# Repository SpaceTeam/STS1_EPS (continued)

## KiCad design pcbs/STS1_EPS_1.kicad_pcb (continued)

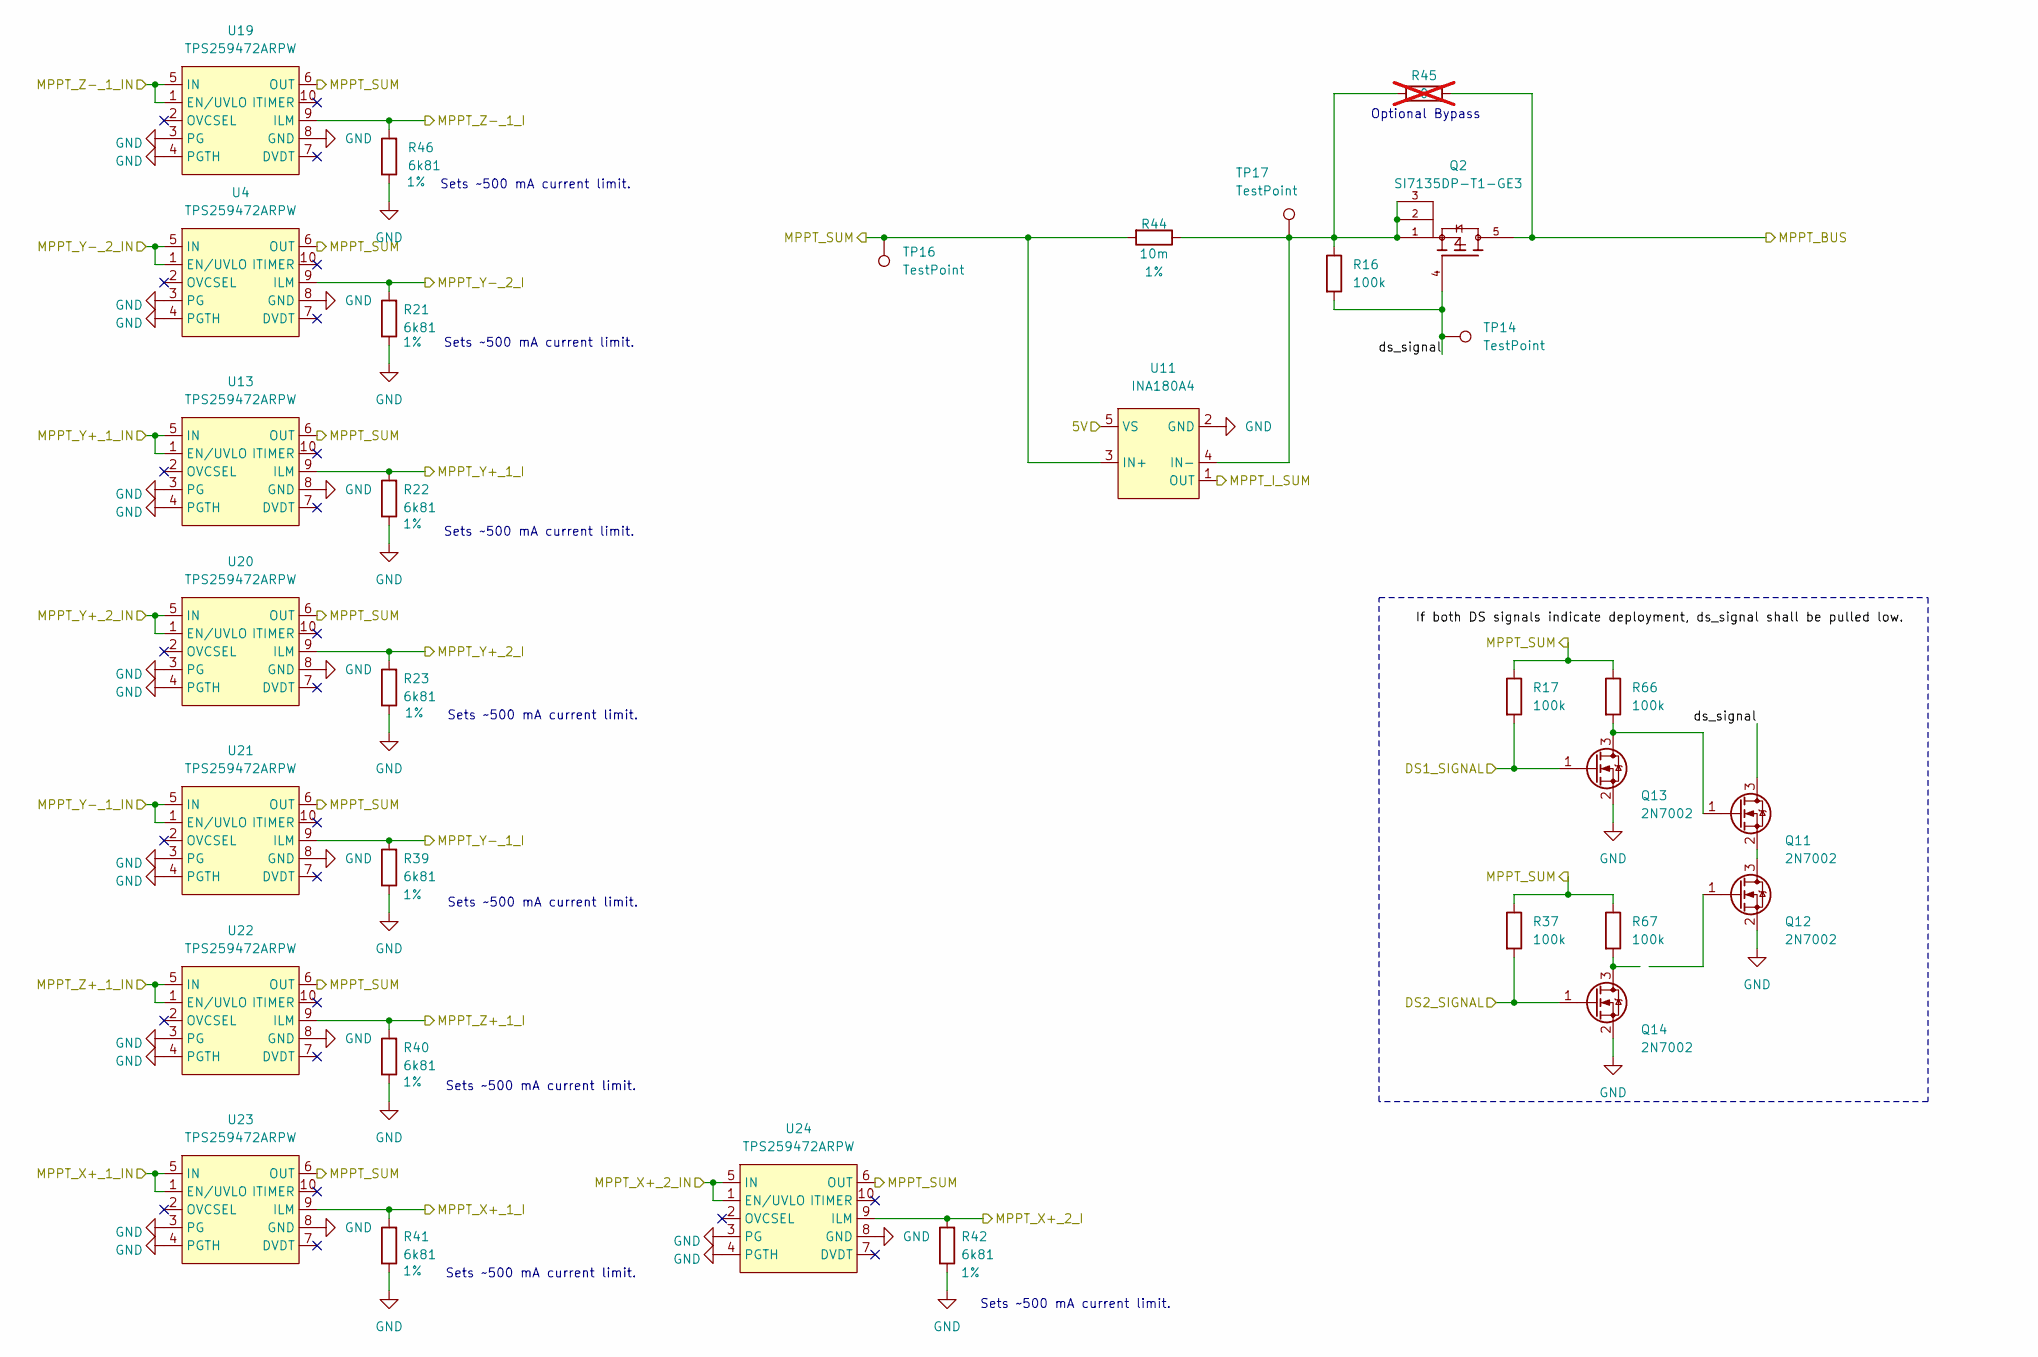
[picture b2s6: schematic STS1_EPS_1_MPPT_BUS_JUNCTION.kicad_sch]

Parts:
Q2: SI7135DP-T1-GE3; POWERPAK_SO8_single; PARTREV A
Q11, Q12, Q13, Q14: 2N7002; SOT-23
R16, R17, R37, R66, R67: 100k; R_0805_2012Metric; Part Nr. TNPW0805100KFEEA
R21, R22, R23, R39, R40, R41, R42, R46: 6k81; R_0805_2012Metric; Tolerance 1%; Part Nr. MCU08050C6811FP500
R44: 10m; R_0805_2012Metric; Tolerance 1%; Part Nr. WFC0805R0100FE66
R45: 0; R_0805_2012Metric; not fitted
TP14, TP16, TP17: TestPoint; TestPoint_THTPad_D1.0mm_Drill0.5mm
U4, U13, U19, U20, U21, U22, U23, U24: TPS259472ARPW; TPS259472ARPWR
U11: INA180A4; SOT-23-5

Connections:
/+5V: U11.5 (VS); also elsewhere on the board
/DS1_SIGNAL_1: Q2.4, Q11.3 (D), R16.2, TP14.1 (1_1); also elsewhere on the board
/DS2_SIGNAL_1: Q13.1 (G), R17.2; also elsewhere on the board
/MPPT_BUS: Q14.1 (G), R37.2; also elsewhere on the board
/MPPT_I_SUM: U11.1 (OUT); also elsewhere on the board
/MPPT_X+_1_I: R41.2, U23.9 (ILM); also elsewhere on the board
/MPPT_X+_2_I: R42.2, U24.9 (ILM); also elsewhere on the board
/MPPT_Y+_1_I: R22.2, U13.9 (ILM); also elsewhere on the board
/MPPT_Y+_2_I: R23.2, U20.9 (ILM); also elsewhere on the board
/MPPT_Y-_1_I: R39.2, U21.9 (ILM); also elsewhere on the board
/MPPT_Y-_2_I: R21.2, U4.9 (ILM); also elsewhere on the board
/MPPT_Z+_1_I: R40.2, U22.9 (ILM); also elsewhere on the board
/MPPT_Z-_1_I: R46.2, U19.9 (ILM); also elsewhere on the board
/Panel_X+_3: U23.1 (EN/UVLO), U23.5 (IN); also elsewhere on the board
/Panel_X+_6: U24.1 (EN/UVLO), U24.5 (IN); also elsewhere on the board
/Panel_Y+_3: U13.1 (EN/UVLO), U13.5 (IN); also elsewhere on the board
/Panel_Y+_6: U20.1 (EN/UVLO), U20.5 (IN); also elsewhere on the board
/Panel_Y-_3: U21.1 (EN/UVLO), U21.5 (IN); also elsewhere on the board
/Panel_Y-_6: U4.1 (EN/UVLO), U4.5 (IN); also elsewhere on the board
/Panel_Z+_3: U22.1 (EN/UVLO), U22.5 (IN); also elsewhere on the board
/Panel_Z-_3: U19.1 (EN/UVLO), U19.5 (IN); also elsewhere on the board
GND: Q12.2 (S), Q13.2 (S), Q14.2 (S), R21.1, R22.1, R23.1, R39.1, R40.1, R41.1, R42.1, R46.1, U4.3 (PG), U4.4 (PGTH), U4.8 (GND), U11.2 (GND), U13.3 (PG), U13.4 (PGTH), U13.8 (GND), U19.3 (PG), U19.4 (PGTH), U19.8 (GND), U20.3 (PG), U20.4 (PGTH), U20.8 (GND), U21.3 (PG), U21.4 (PGTH), U21.8 (GND), U22.3 (PG), U22.4 (PGTH), U22.8 (GND), U23.3 (PG), U23.4 (PGTH), U23.8 (GND), U24.3 (PG), U24.4 (PGTH), U24.8 (GND); also elsewhere on the board
unnamed: Q11.1 (G), Q13.3 (D), R66.2
unnamed: Q11.2 (S), Q12.3 (D)
unnamed: Q14.3 (D), R67.2
unnamed: Q2.1, Q2.2, Q2.3, R16.1, R44.1, R45.1, TP17.1 (1_1), U11.4 (IN-)

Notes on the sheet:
Sets ~500 mA current limit.
Optional Bypass

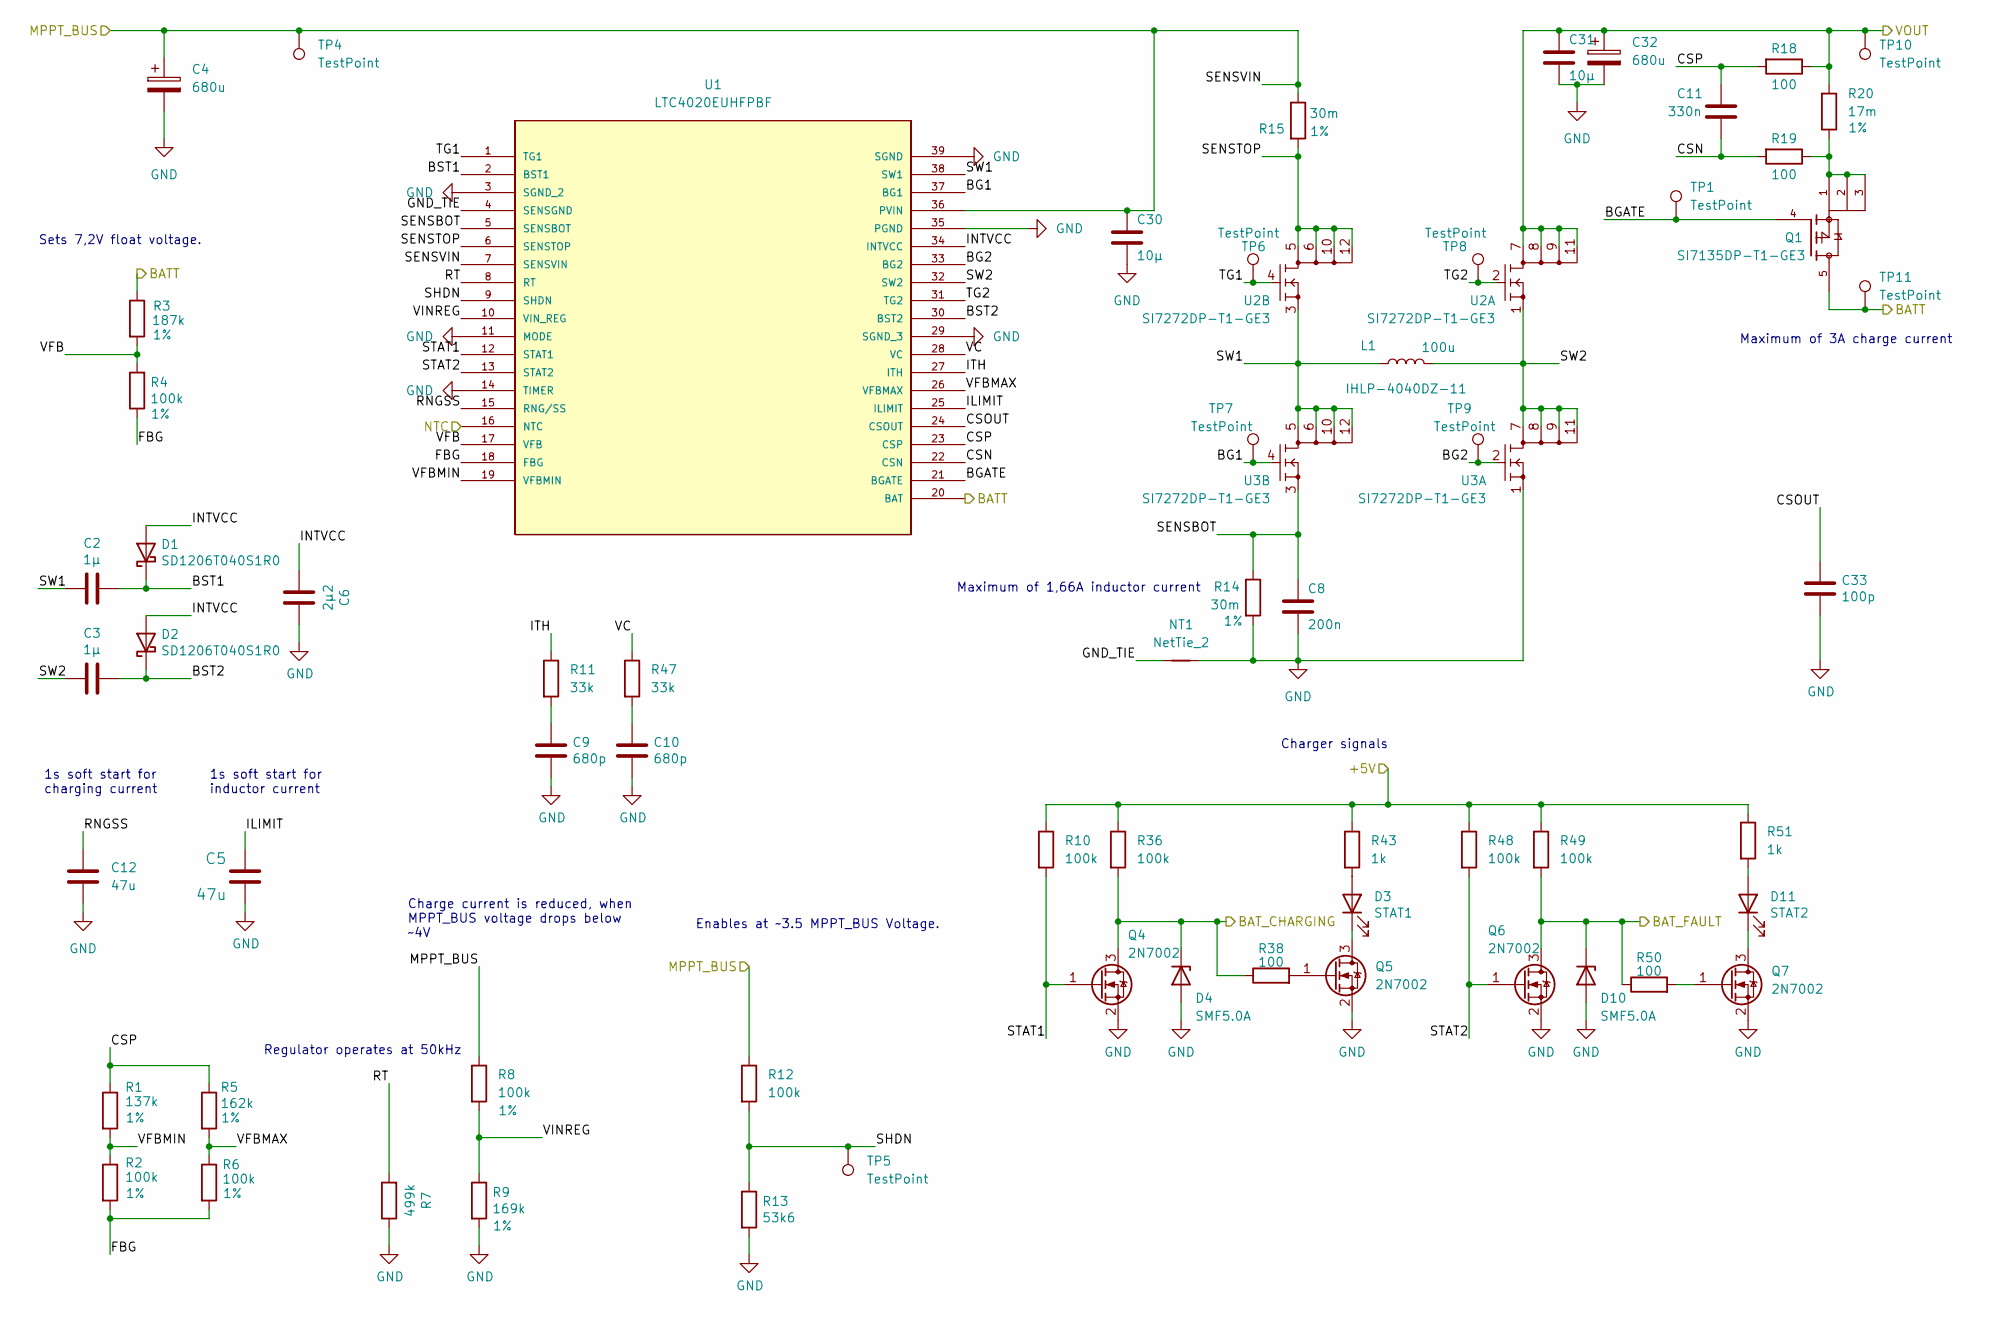
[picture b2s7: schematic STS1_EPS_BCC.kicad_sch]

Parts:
C2, C3: 1µ; C_0805_2012Metric; Part Nr. C0805T105K4RALTU
C4, C32: 680u; CP_EIA-7343-43_Kemet-X; Part Nr. TPSE687M010R0150V
C5, C12: 47u; CP_EIA-3528-12_Kemet-T; Part Nr. TP3B476K010C1800AS
C6: 2µ2; C_0805_2012Metric; Part Nr. C0805T225K4RACTU
C8: 200n; C_0805_2012Metric; Part Nr. GCM219R71C204JA37J
C9, C10: 680p; C_0805_2012Metric; Part Nr. 08051C681JAT2A
C11: 330n; C_0805_2012Metric; Part Nr. C0805T334K3RCLTM
C30, C31: 10µ; C_0805_2012Metric; Part Nr. CM21X7R106K06AT
C33: 100p; C_0805_2012Metric; Part Nr. C0805T104J5RALTU
D1, D2: SD1206T040S1R0; D_1206_3216Metric; Part Nr. SD1206T040S1R0
D3: STAT1; LED_0805_2012Metric
D4, D10: SMF5.0A; D_SMF; Part Nr. SMF5.0A
D11: STAT2; LED_0805_2012Metric
L1: 100u; L_Vishay_IHLP-4040; Part IHLP-4040DZ-11
NT1: NetTie_2; NetTie-2_SMD_Pad0.5mm
Q1: SI7135DP-T1-GE3; POWERPAK_SO8_single; PARTREV A
Q4, Q5, Q6, Q7: 2N7002; SOT-23; Part Nr. 2N7002
R1: 137k; R_0805_2012Metric; Tolerance 1%; Part Nr. CR0805-FX-1373ELF
R2, R4, R6, R8: 100k; R_0805_2012Metric; Tolerance 1%; Part Nr. TNPW0805100KFEEA
R3: 187k; R_0805_2012Metric; Tolerance 1%; Part Nr. AA0805FR-07187KL
R5: 162k; R_0805_2012Metric; Tolerance 1%; Part Nr. CR0805-FX-1623ELF
R7: 499k; R_0805_2012Metric; Part Nr. CR0805-FX-4993ELF
R9: 169k; R_0805_2012Metric; Tolerance 1%; Part Nr. RE0805FRE07169KL
R10, R12, R36, R48, R49: 100k; R_0805_2012Metric; Part Nr. TNPW0805100KFEEA
R11, R47: 33k; R_0805_2012Metric; Part Nr. KTR10EZPF3302
R13: 53k6; R_0805_2012Metric; Part Nr. CR0805-FX-5362ELF
R14, R15: 30m; R_0805_2012Metric; Tolerance 1%; Part Nr. WSL0805R0300FEA
R18, R19, R38, R50: 100; R_0805_2012Metric; Part Nr. TNPW0805100RFETA
R20: 17m; R_1206_3216Metric; Tolerance 1%; Part Nr. PE1206FRF7W0R017L
R43, R51: 1k; R_0805_2012Metric; Part Nr. CRT0805AFY-1001ELF
TP1, TP4, TP5, TP6, TP7, TP8, TP9, TP10, TP11: TestPoint; TestPoint_THTPad_D1.0mm_Drill0.5mm
U1: LTC4020EUHFPBF; AD_QFN-38_UHF; MANUFACTURER_PART_NUMBER ltc4020euhf#pbf
U2, U3: SI7272DP-T1-GE3; POWERPAK_SO8

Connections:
/+5V: R10.1, R36.1, R43.1, R48.1, R49.1, R51.1; also elsewhere on the board
/BATT: Q1.5, R3.1, TP11.1 (1_1), U1.20 (BAT); also elsewhere on the board
/BAT_CHARGING: D4.1 (K), Q4.3 (D), R36.2, R38.1; also elsewhere on the board
/BAT_FAULT: D10.1 (K), Q6.3 (D), R49.2, R50.1; also elsewhere on the board
/Battery Charge Controller/BG1: TP7.1 (1_1), U1.37 (BG1), U3.4 (G2)
/Battery Charge Controller/BG2: TP9.1 (1_1), U1.33 (BG2), U3.2 (G1)
/Battery Charge Controller/BGATE: Q1.4, TP1.1 (1_1), U1.21 (BGATE)
/Battery Charge Controller/BST1: C2.1, D1.1 (K), U1.2 (BST1)
/Battery Charge Controller/BST2: C3.1, D2.1 (K), U1.30 (BST2)
/Battery Charge Controller/CSN: C11.2, R19.2, U1.22 (CSN)
/Battery Charge Controller/CSOUT: C33.1, U1.24 (CSOUT)
/Battery Charge Controller/CSP: C11.1, R1.1, R5.1, R18.2, U1.23 (CSP)
/Battery Charge Controller/FBG: R2.2, R4.1, R6.2, U1.18 (FBG)
/Battery Charge Controller/GND_TIE: NT1.1, U1.4 (SENSGND)
/Battery Charge Controller/ILIMIT: C5.2, U1.25 (ILIMIT)
/Battery Charge Controller/INTVCC: C6.2, D1.2 (A), D2.2 (A), U1.34 (INTVCC)
/Battery Charge Controller/ITH: R11.1, U1.27 (ITH)
/Battery Charge Controller/RNGSS: C12.1, U1.15 (RNG/SS)
/Battery Charge Controller/RT: R7.2, U1.8 (RT)
/Battery Charge Controller/SENSBOT: C8.2, R14.1, U1.5 (SENSBOT), U3.3 (S2)
/Battery Charge Controller/SENSTOP: R15.2, U1.6 (SENSTOP), U2.5 (D2_1), U2.6 (D2_2), U2.10 (D2_3), U2.12 (D2_4)
/Battery Charge Controller/SHDN: R12.2, R13.1, TP5.1 (1_1), U1.9 (SHDN)
/Battery Charge Controller/STAT1: Q4.1 (G), R10.2, U1.12 (STAT1)
/Battery Charge Controller/STAT2: Q6.1 (G), R48.2, U1.13 (STAT2)
/Battery Charge Controller/SW1: C2.2, L1.1, U1.38 (SW1), U2.3 (S2), U3.5 (D2_1), U3.6 (D2_2), U3.10 (D2_3), U3.12 (D2_4)
/Battery Charge Controller/SW2: C3.2, L1.2, U1.32 (SW2), U2.1 (S1), U3.7 (D1_1), U3.8 (D1_2), U3.9 (D1_3), U3.11 (D1_4)
/Battery Charge Controller/TG1: TP6.1 (1_1), U1.1 (TG1), U2.4 (G2)
/Battery Charge Controller/TG2: TP8.1 (1_1), U1.31 (TG2), U2.2 (G1)
/Battery Charge Controller/VC: R47.1, U1.28 (VC)
/Battery Charge Controller/VFB: R3.2, R4.2, U1.17 (VFB)
/Battery Charge Controller/VFBMAX: R5.2, R6.1, U1.26 (VFBMAX)
/Battery Charge Controller/VFBMIN: R1.2, R2.1, U1.19 (VFBMIN)
/Battery Charge Controller/VINREG: R8.2, R9.1, U1.10 (VIN_REG)
/Battery Charge Controller/VOUT: C31.2, C32.1, R18.1, R20.2, TP10.1 (1_1), U2.7 (D1_1), U2.8 (D1_2), U2.9 (D1_3), U2.11 (D1_4); also elsewhere on the board
/MPPT_BUS: C4.1, C30.2, R8.1, R12.1, R15.1, TP4.1 (1_1), U1.7 (SENSVIN), U1.36 (PVIN); also elsewhere on the board
/NTC: U1.16 (NTC); also elsewhere on the board
GND: C4.2, C5.1, C6.1, C8.1, C9.2, C10.2, C12.2, C30.1, C31.1, C32.2, C33.2, D4.2 (A), D10.2 (A), NT1.2, Q4.2 (S), Q5.2 (S), Q6.2 (S), Q7.2 (S), R7.1, R9.2, R13.2, R14.2, U1.3 (SGND_2), U1.11 (MODE), U1.14 (TIMER), U1.29 (SGND_3), U1.35 (PGND), U1.39 (SGND), U3.1 (S1); also elsewhere on the board
unnamed: C9.1, R11.2
unnamed: C10.1, R47.2
unnamed: D3.2 (A), R43.2
unnamed: D3.1 (K), Q5.3 (D)
unnamed: D11.2 (A), R51.2
unnamed: D11.1 (K), Q7.3 (D)
unnamed: Q1.1, Q1.2, Q1.3, R19.1, R20.1
unnamed: Q5.1 (G), R38.2
unnamed: Q7.1 (G), R50.2

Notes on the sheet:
Charger signals
Regulator operates at 50kHz
Sets 7,2V float voltage.
Charge current is reduced, when MPPT_BUS voltage drops below ~4V
Maximum of 1,66A inductor current
Enables at ~3.5 MPPT_BUS Voltage.
1s soft start for inductor current
1s soft start for charging current
Maximum of 3A charge current

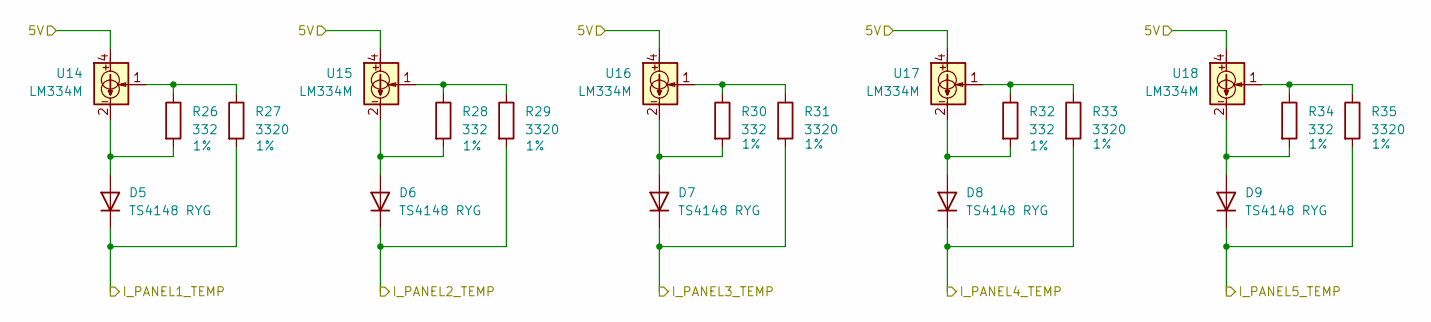
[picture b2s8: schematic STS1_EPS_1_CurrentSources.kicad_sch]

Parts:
D5, D6, D7, D8, D9: TS4148 RYG; D_0805_2012Metric; Part Nr. TS4148 RYG
R26, R28, R30, R32, R34: 332; R_0805_2012Metric; Tolerance 1%; Part Nr. RT0805FRE07332RL
R27, R29, R31, R33, R35: 3320; R_0805_2012Metric; Tolerance 1%; Part Nr. RT0805FRE073K32L
U14, U15, U16, U17, U18: LM334M; SOIC-8_3.9x4.9mm_P1.27mm

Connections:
/+5V: U14.4, U15.4, U16.4, U17.4, U18.4; also elsewhere on the board
/Panel_X+_5: D9.1 (K), R35.2; also elsewhere on the board
/Panel_Y+_5: D8.1 (K), R33.2; also elsewhere on the board
/Panel_Y-_5: D7.1 (K), R31.2; also elsewhere on the board
/Panel_Z+_5: D6.1 (K), R29.2; also elsewhere on the board
/Panel_Z-_5: D5.1 (K), R27.2; also elsewhere on the board
unnamed: D5.2 (A), R26.2, U14.2, U14.3, U14.6, U14.7
unnamed: D6.2 (A), R28.2, U15.2, U15.3, U15.6, U15.7
unnamed: D7.2 (A), R30.2, U16.2, U16.3, U16.6, U16.7
unnamed: D8.2 (A), R32.2, U17.2, U17.3, U17.6, U17.7
unnamed: D9.2 (A), R34.2, U18.2, U18.3, U18.6, U18.7
unnamed: R26.1, R27.1, U14.1
unnamed: R28.1, R29.1, U15.1
unnamed: R30.1, R31.1, U16.1
unnamed: R32.1, R33.1, U17.1
unnamed: R34.1, R35.1, U18.1

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
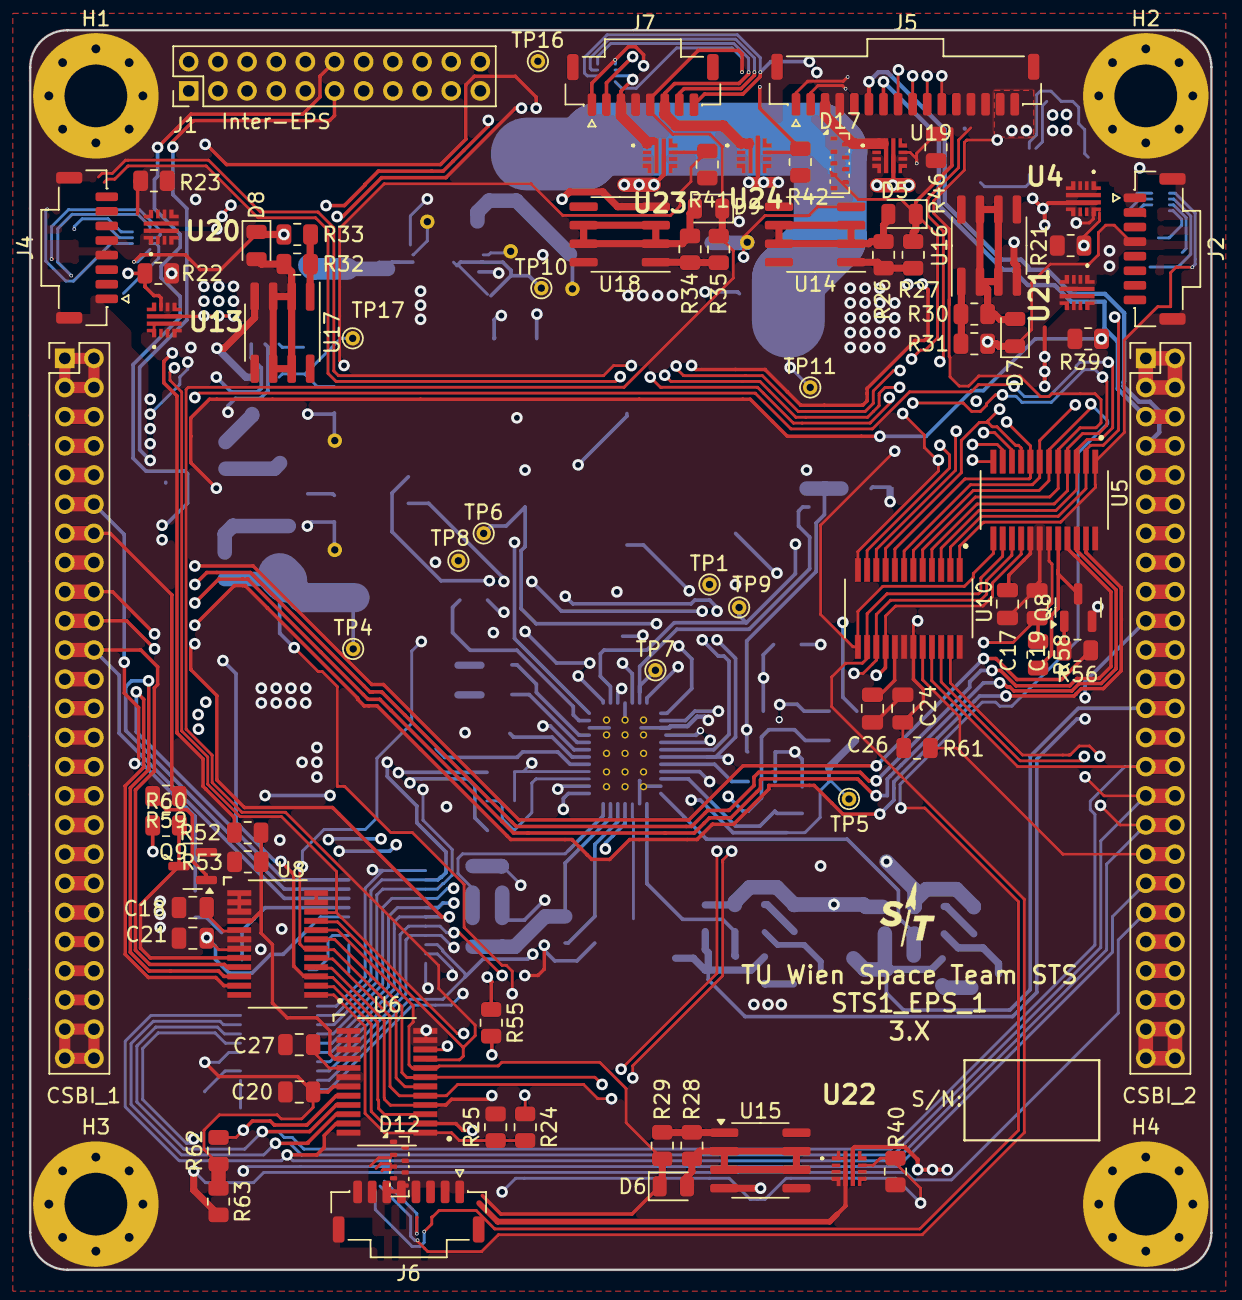
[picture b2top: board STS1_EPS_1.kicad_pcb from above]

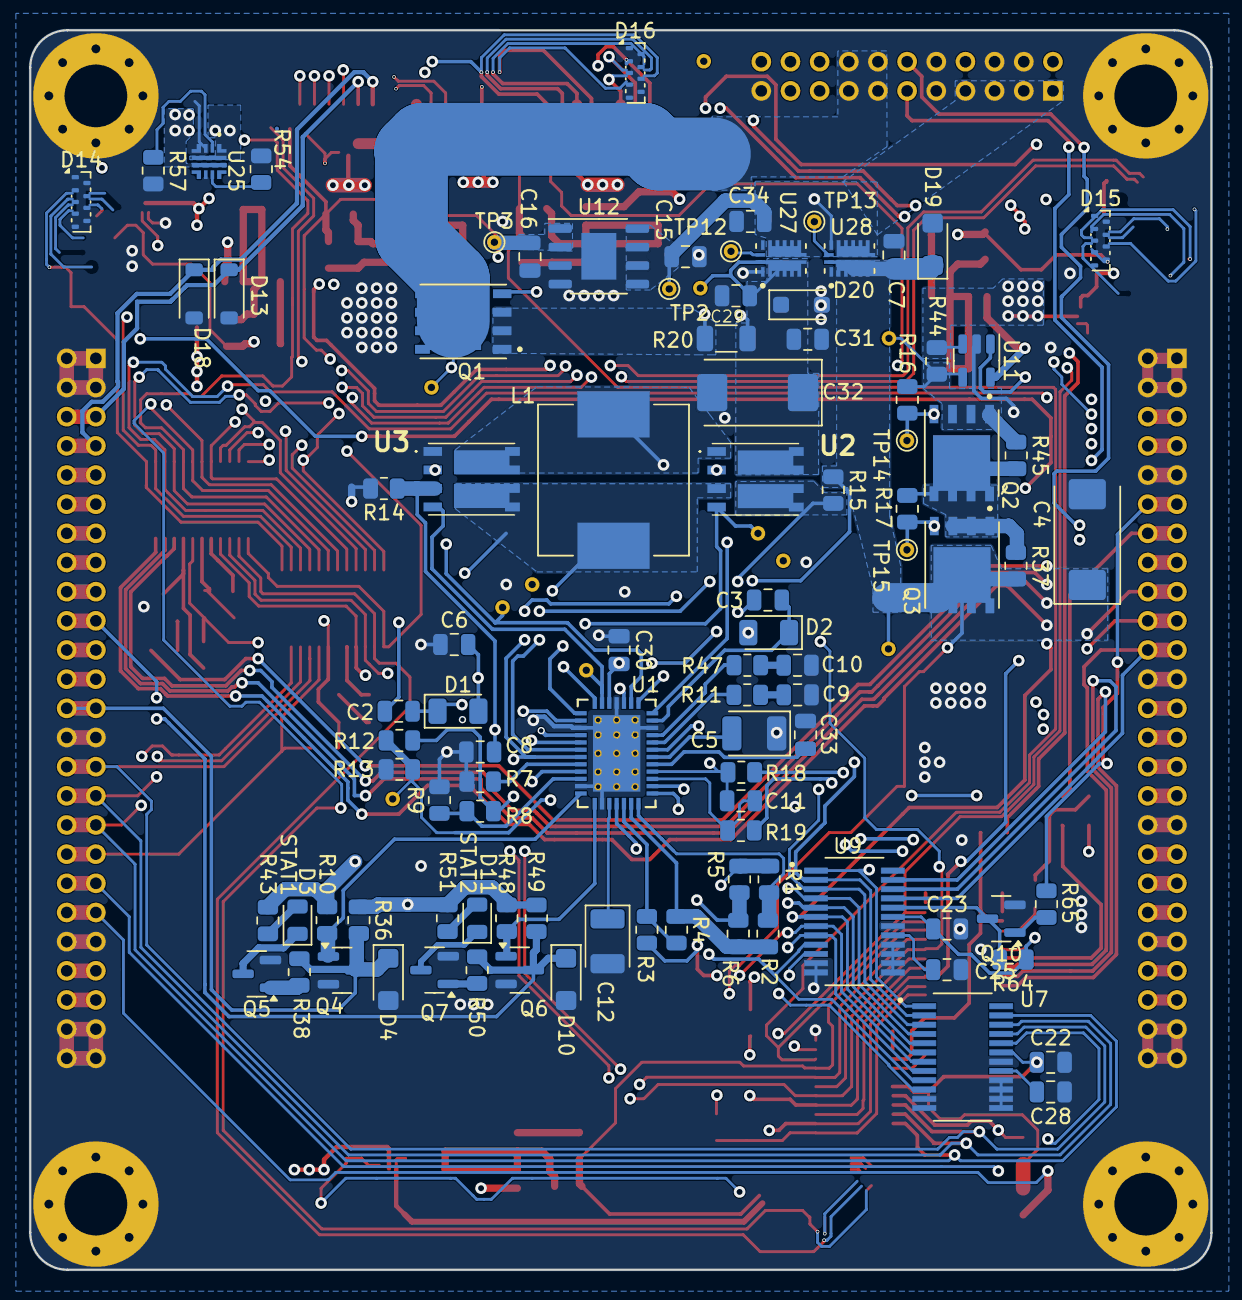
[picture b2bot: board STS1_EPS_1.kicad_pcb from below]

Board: 6 copper layers, 81.0 x 85.0 mm, 184 parts (97 on the bottom side), 158 nets.

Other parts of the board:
Q3: SI7135DP-T1-GE3; POWERPAK_SO8_single
TP15: TestPoint; TestPoint_THTPad_D1.0mm_Drill0.5mm

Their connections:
/DS2_SIGNAL_1: Q3.4, TP15.1 (1_1); also elsewhere on the board
/MPPT_BUS: Q3.5; also elsewhere on the board

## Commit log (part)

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2022-05-12 Added KiCad projects.
2022-05-12 Added STS1_PCB_LIBRARY as a git submodule.
2022-05-15 Added libraries.
2022-06-06 Worked on STS1_EPS.
2022-06-08 Worked on STS1_EPS_1.
2022-06-08 Bumped libs repo.
2022-06-08 Worked on STS_EPS_1.
2022-06-28 Worked on STS1_EPS_1 and began work on STS1_EPS_2.
2022-06-29 Finished first revision of schematic.
2022-07-04 Worked on STS1_EPS_2 layout.
2022-07-06 Worked on STS1_EPS_1 layout.
2022-07-06 Bumped sub-repo.
2022-07-08 Bumped subrepo.
2022-07-13 Made STS1_EPS_2 inter EPS connector consistent to STS1_EPS_1.
2022-07-14 EPS_2 Layout nearly finished, alot DRC Errors
2022-07-14 EPS_2 removes some DRC errors, added Areas
    sry for bad commit messages
2022-07-16 Finished routing of STS1_EPS_1. DRC of layout is still outstanding.
2022-07-17 Cleared all DRC errors of STS1_EPS_1.
2022-07-17 Reworked STS1_EPS_2. - Added Capacitor bank - Thickened some load bearing copper traces.
2022-07-17 Added test points to STS1_EPS_2.
2022-07-17 Added testpoints to STS1_EPS_1.
2022-07-20 Solder mask was incorrectly set for U27 and U28 of STS1_EPS_1. Fixed that.
2022-07-26 Added part numbers to some of the components. No functional changes.
2023-06-13 Added some missing 3d files.
2023-08-23 Renamed STS1_EPS_2 to STS1_EPS_3.
2023-08-26 Revert "Renamed STS1_EPS_2 to STS1_EPS_3."
    This reverts commit 47631bb2a940810a2f7b8517a6bea59395bf86b8.
2023-08-29 worked on sts1_eps_1
2023-09-17 Worked on STS1_EPS_1 and STS1_EPS_2.
2023-09-17 STS1_EPS_1 no errors.
2023-09-17 Worked on STS1_EPS_2.
2023-09-19 STS1_EPS_2 no errors.
2023-09-20 Added a logic voltage, so that the deployment circuit breaker FETs also work, when battery is fails.
2023-09-27 Moved the battery connector a bit, so that it does not collide with the inter-eps connector. Also resolved all warnings in the layout.
2023-10-05 Minor changes.
2023-10-16 Adjusted position of the x- panel connector.
2023-10-26 Added part numbers to CSBI and inter EPS connectors. Also added some missing 3d files.
2023-10-29 Changed connectors of STS_EPS_1 ...again.
2023-11-11 Added CC BY 4.0 license.
2024-04-14 Ported kicad projects to KiCad 8.0.
2024-04-14 Changed some footprints that had the wrong shape in EPS 2.1.
2024-04-16 Rewired a falsely connected deployment switch.
2024-06-04 Intermediate commit.
2024-06-04 Added test points around MPPT bus current sense resistor.
2024-06-04 Added test point directly at battery and after switch.
2024-06-06 Adjusted CSBI so it conforms to the new version of it.
2024-06-08 Signals to the bus gate should now be provided with supply voltage the proper way.
2024-06-08 Added possibilities to short single interrupt sources.
2024-06-10 Fixed the logic behing the GATE_SIGNAL signal.
2024-07-18 Removed UCI connector from STS1_EPS_2 and merged UCI connector with J5 on STS1_EPS_1.
2024-07-22 Added TVS diodes.
2024-07-22 Added even more ESD protection.
2024-07-23 Reoriented coordinate system.
2024-08-06 Fixed some warnings and errors.
2024-08-07 Fixed warnings and errors.
2024-08-27 STS1_EPS_1 now without errors.
2024-09-02 Reduced both EPS PCBs down to 0 DRC errors.
2024-09-02 - Fixed some minor warnings - Moved C4 on STS1_EPS_1, so it no longer collides with the COBC. - Bumped library sub repo.
2024-09-05 Added part numbers for some ESD diodes.
2024-09-12 Added 3D models to some footprints.
2024-09-14 Fixed diode values for good.
2024-09-14 Made the label names at the UCI connector more consistent.
2024-09-14 Removed the ideal diodes at the UCI UART RX/TX lines. Added TVS diodes to those lines.
2024-09-14 Added tolerances to some resistors that should be precise.
2024-09-14 Modified some resistor values slightly, so that they fall in common resistor series.
2024-09-14 Marked optional bypasses as "Do not place".
2024-09-16 Added values to the capacitors of the capacitor bank.
2024-09-16 Added part number to fuse.
2024-09-16 Logic gates now use ISO symbols consistently.
2024-09-17 Separated the SHDN pins of the logic- and power oring. Also added TVS diodes to them, as this is recommended by the datasheet.
2024-09-18 Added a linear regulator to the power oring in STS1_EPS_2, since the components supplied by that power oring could not withstand that voltage.
2024-10-12 Added python script for replacing labels within KiCad.
2024-10-12 Reverted two files to before the label change.
2024-10-12 Changed net labels of the panel connectors, so they are consistent with the name of the respective connector.
2024-10-16 Started adding part numbers to passive components.
2024-10-20 Added part numbers to components of STS1_EPS_1.
2024-10-22 Added more part numbers.
2024-12-08 Fixed footprint of U3 and U6 on STS1_EPS_2.
2025-01-09 * New symbol for U4 and U5 on STS1_EPS_2. * Made the tracing for U4 and U5 a bit better.
2025-08-26 Fixed deployment timer symbol having wrong pin numbers.
2025-08-27 Fixed inhibit logic.
2025-08-28 Fixed layout after changes to inhibit logic.
2025-08-28 * Added resistor in front of NTC channel of both ADCs. * Changed signal name from ~BATT_INHIBIT to BATT_INHIBIT.
2025-09-07 Added FETs to the CS pins of the EDU's housekeeping data interface.
2025-09-07 * Cell balancer is now deactivated by UVLO signal, rather than bat fault signal * Bat Fault signal is now an open drain output
2025-09-07 Fixed inhibit logic, again...
2025-09-07 Added resistor for the RBF pin.
2025-12-31 Updated a few inconsistent part numbers.
2026-04-15 feat(EPS PCB 2): start redesign & cleanup for less idle power consumption
